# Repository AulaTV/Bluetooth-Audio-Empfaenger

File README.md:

# Bluetooth-Audio-Empfaenger
Bluetooth Audio Empfänger mit dem CSR8645 Chipset

Dieser Bluetooth Empfänger wird in der Aula zum Einsatz kommen, um Audiodateien unkompliziert vom Smartphone aus über die Beschallungsanlage abspielen zu können.
Um den Empfänger optimal an seinen Einsatzzweck anpassen zu können, wurde der CSR8645 Chip gewählt.
Dieser lässt sich mit überschaubarem Aufwand selbst programmieren, d.h. Name und Verhalten lassen sich frei einstellen.

### Übersicht über die Konnektivität:
- DC-Eingang (6 - 24 V)
- Audio-Ausgang (3,5 mm Klinkenbuchse)
- RP-SMA Antennenanschluss
- USB Buchse zur Programmierung
- SUB-D Buchse (9-polig) zur Steuereinheit

Der Empfänger befindet sich derzeit im Aufbau :-)

## Notizen/Nützliches:

verwendete Software:
- CSR8600 ROM Series Configuration Tool (3.0.64)
- BlueCore Persistent Store (PSTool)
-

eBay Link zum Modul:
http://www.ebay.de/itm/APT-X-Bluetooth-4-0-Audio-Receiver-Board-Wireless-Stereo-Music-Module-iPhone-PC-/131999036518?hash=item1ebbc17466:g:G6AAAOSwpDdVFmyN

FT232RL Adapter:
http://www.ebay.de/itm/FTDI-FT232RL-USB-zu-TTL-Serien-Converter-Adapter-Modul-5V-3-3V-Fuer-Arduino-/172346455693

Gehäuse (Hammond 1551KFL)
https://www.reichelt.de/Kunststoffgehaeuse-HAMMOND/1551KFLBK/3/index.html?ACTION=3&LA=446&ARTICLE=121028&GROUPID=7721&artnr=1551KFLBK&SEARCH=1551kflbk

Weitere Infos/interessante Links:
https://github.com/lorf/csr-spi-ftdi/

Class of Device:
http://www.ampedrftech.com/cod.htm

to be continued ...

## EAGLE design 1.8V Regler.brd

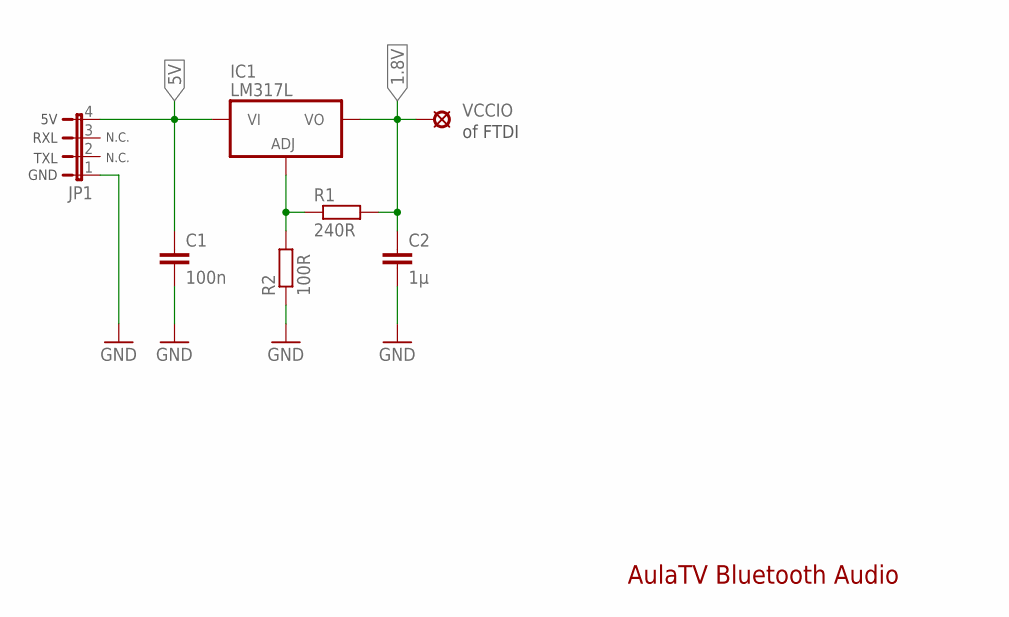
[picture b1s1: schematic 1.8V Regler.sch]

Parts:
C1: 100n; C0805
C2: 1µ; C0805
IC1: LM317L; TO92TAPE
JP1: JP4E; JP4
R1: 240R; R0805
R2: 100R; R0805
VCCIO: VCCIO; LSP10

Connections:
1.8V: C2.1, IC1.P$3 (VO), R1.2, VCCIO.MP
5V: C1.1, IC1.P$2 (VI), JP1.4
GND: C1.2, C2.2, JP1.1, R2.1
unnamed: IC1.P$1 (ADJ), R1.1, R2.2

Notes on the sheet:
of FTDI
N.C.
RXL
TXL
GND
AulaTV Bluetooth Audio

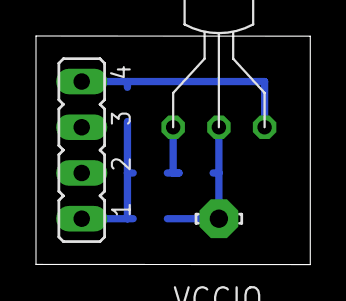
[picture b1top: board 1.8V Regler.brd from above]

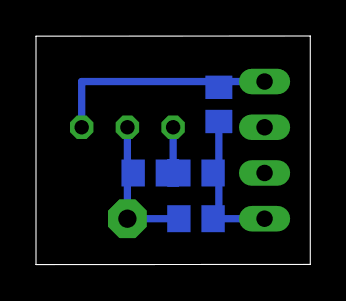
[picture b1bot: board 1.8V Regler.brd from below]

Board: 2 copper layers, 15.2 x 12.7 mm, 7 parts (4 on the bottom side), 4 nets.

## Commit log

2017-07-31 Update README.md
    inclueded Link to interesting repository about flashing the Chip
2017-07-31 Upload .psr dump of original module
2017-08-04 added eagle files for 1.8V regulator for interfacing with the CSR8645 chip.
    Generates 1.8V from 5V (USB) to supply the I/O logic of the FTDI USB-UART chip (FT232RL).
2017-08-04 Create hardwareDummy
2017-08-04 Rename 1.8V Regler.brd to hardware/1.8V Regler.brd
2017-08-04 Rename 1.8V Regler.sch to hardware/1.8V Regler.sch
2017-08-04 Rename dump.psr to software/dump.psr
2017-08-08 Rename software/dump.psr to software/original/dump.psr
2017-08-08 Rename software/name_modified.psr to software/modified/name_modified.psr
